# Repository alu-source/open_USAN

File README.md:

## Summary

1. Overview
2. Build instructions
3. Testing and validation 

## 1. Overview

The goal of this project was to create a low cost small scale 2D ultrasonic anenomter. The resulting solution is based on a STM32F4 microcontroller and uses off the shelf electrical components with a cost of around 100€, and offers multiple IO options for data output, a USB interface, a dual-channel analog output, and a synchronization signal input. The sensor can be configured with various parameters and a maximum measurement frequency of 100 Hz can be achieved.
A detailed explanation of the working principle and the technique used can be found in my <a href="/Documentation/Bachelor_thesis.pdf" target="_blank">thesis</a>. 
<br/><br/>
A brief explanation:

The speed of sound and the airspeed are calculated with the help of two ultrasound transmissions in opposite directions, the mean measured speed for both transmissions is the speed of sound and the difference to the mean is the airspeed.

To accurately calculate the speed of the transmissions, the time of flight (ToF) between transmission and reception must be accurately measured, which requires some neat digital signal processing.
The sensor can be used and configured via serial terminal, all commands and expected behaviour are given in the manual.

## 2. Build instructions
### Hardware
KiCad has been used for the PCB design, the design files and a production-ready export can be found in the Hardware folder.
The PCB can be manufactured by most common PCB manufacturing services such as JLCPCB or Aisler. There are two different types of PCB, a two layer PCB for mounting the transceivers and a four layer PCB for the main board. All components can be soldered by hand, although reflow soldering (using a hot plate or hot air) is highly recommended.
Most components are available from Mouser. The resistors should be 1% accurate and the ceramic capacitors should have a minimum nominal voltage rating of 24V.

The other part of the hardware consists of 3D printed parts and M3 screws.
The arms are glued into the body to create a watertight connection, an epoxy glue should be used. 

### Software
The software devlopment was done in Segger embeded studio the files can be found in the Software folder.
Further configuartion parameters can be set in the sensor_config.h file.
This makes it possible to change the transceiver or to modify the geometry of the sensor.

Using the USB interface, different runmodes an trigger/sample times can be configured, for more information look in to the [manual](https://github.com/alu-source/open-USAN/blob/main/Documentation/Manual/Ultrasonic%20Anemometer%20Reference%20Manual.docx).

## 3. Testing and Validation

Testing and validation was carried out in a wind tunnel capable of generating air speeds of up to 45 m/s.
A prantle tube and a Dantec high pression anemometer were used for velocity measurements.

In the first test, a velocity deficit was detected near the transceiver mounting location due to transceiver blockage, as shown below. 

The left plot shows the measured velocity magnetude and the right plot shows the measurement error of magnitude and angle over the inflow angle. 

In order to counteract this phenomenon, calibration was carried out at various inflow angle and air speeds. 
Each sensor has a slightly different optimum calibration, the data includes an averaged calibration for the sensor which does not give the best sensor performance but eliminates the need to perform a calibration.
A semi-automated [skript] ("/2D-US-Calibration/Skript/Sensor_calibration_and_validation.m") was developed and tested to collect the raw data required for calibration. After calibration, a validation measurement was performed.

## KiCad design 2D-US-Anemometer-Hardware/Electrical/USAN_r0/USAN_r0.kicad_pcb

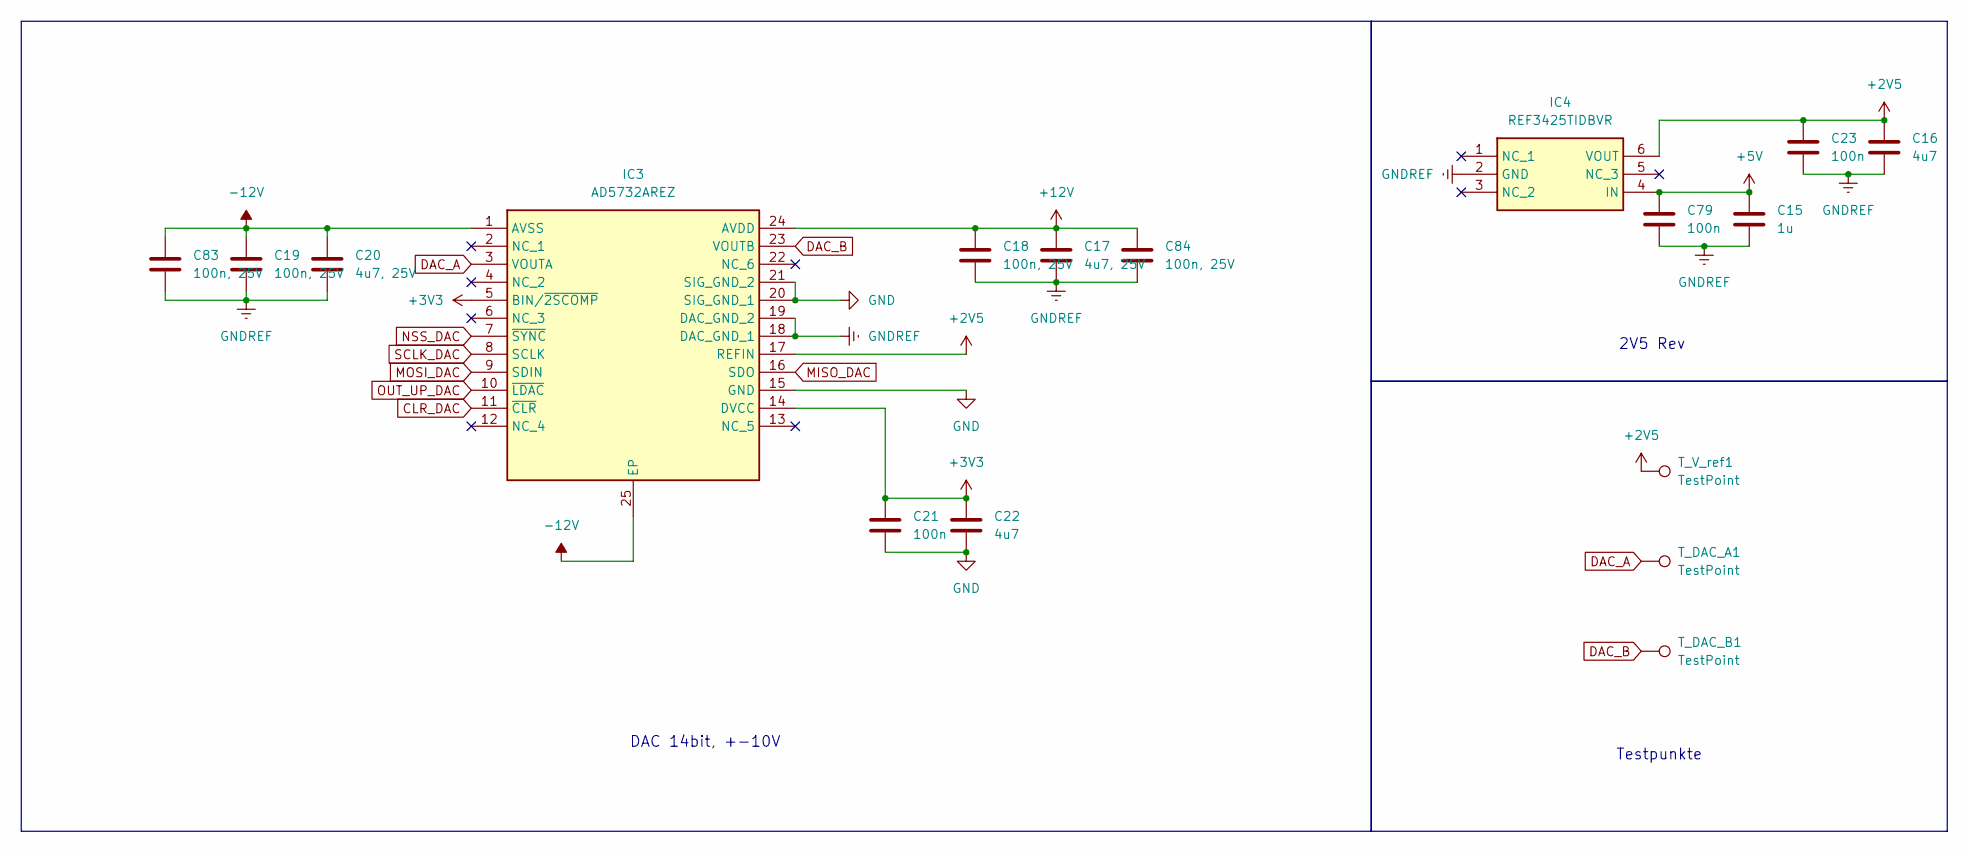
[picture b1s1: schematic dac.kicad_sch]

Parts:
C15: 1u; C_0603_1608Metric
C16, C22: 4u7; C_0805_2012Metric
C17, C20: 4u7, 25V; C_0805_2012Metric
C18, C19, C83, C84: 100n, 25V; C_0603_1608Metric
C21, C23, C79: 100n; C_0603_1608Metric
IC3: AD5732AREZ; SOP65P640X120-25N; Mouser Part Number 584-AD5732AREZ
IC4: REF3425TIDBVR; SOT95P280X145-6N; Mouser Part Number 595-REF3425TIDBVR
T_DAC_A1: TestPoint; TestPoint_Pad_D1.5mm
T_DAC_B1: TestPoint; TestPoint_Pad_D1.5mm
T_V_ref1: TestPoint; TestPoint_Pad_D1.5mm

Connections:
+2V5: C16.1, C23.1, IC3.17 (REFIN), IC4.6 (VOUT), T_V_ref1.1
+3V3: C21.1, C22.1, IC3.5 (BIN/~2SCOMP), IC3.14 (DVCC); also elsewhere on the board
+5V: C15.1, C79.1, IC4.4 (IN); also elsewhere on the board
+12V: C17.1, C18.1, C84.1, IC3.24 (AVDD); also elsewhere on the board
-12V: C19.1, C20.1, C83.1, IC3.1 (AVSS), IC3.25 (EP); also elsewhere on the board
CLR_DAC: IC3.11 (~CLR); also elsewhere on the board
DAC_A: IC3.3 (VOUTA), T_DAC_A1.1; also elsewhere on the board
DAC_B: IC3.23 (VOUTB), T_DAC_B1.1; also elsewhere on the board
GND: C21.2, C22.2, IC3.15 (GND), IC3.20 (SIG_GND_1), IC3.21 (SIG_GND_2); also elsewhere on the board
GNDREF: C15.2, C16.2, C17.2, C18.2, C19.2, C20.2, C23.2, C79.2, C83.2, C84.2, IC3.18 (DAC_GND_1), IC3.19 (DAC_GND_2), IC4.2 (GND); also elsewhere on the board
MISO_DAC: IC3.16 (SDO); also elsewhere on the board
MOSI_DAC: IC3.9 (SDIN); also elsewhere on the board
NSS_DAC: IC3.7 (~SYNC); also elsewhere on the board
OUT_UP_DAC: IC3.10 (~LDAC); also elsewhere on the board
SCLK_DAC: IC3.8 (SCLK); also elsewhere on the board

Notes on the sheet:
2V5 Rev
DAC 14bit, +-10V
Testpunkte

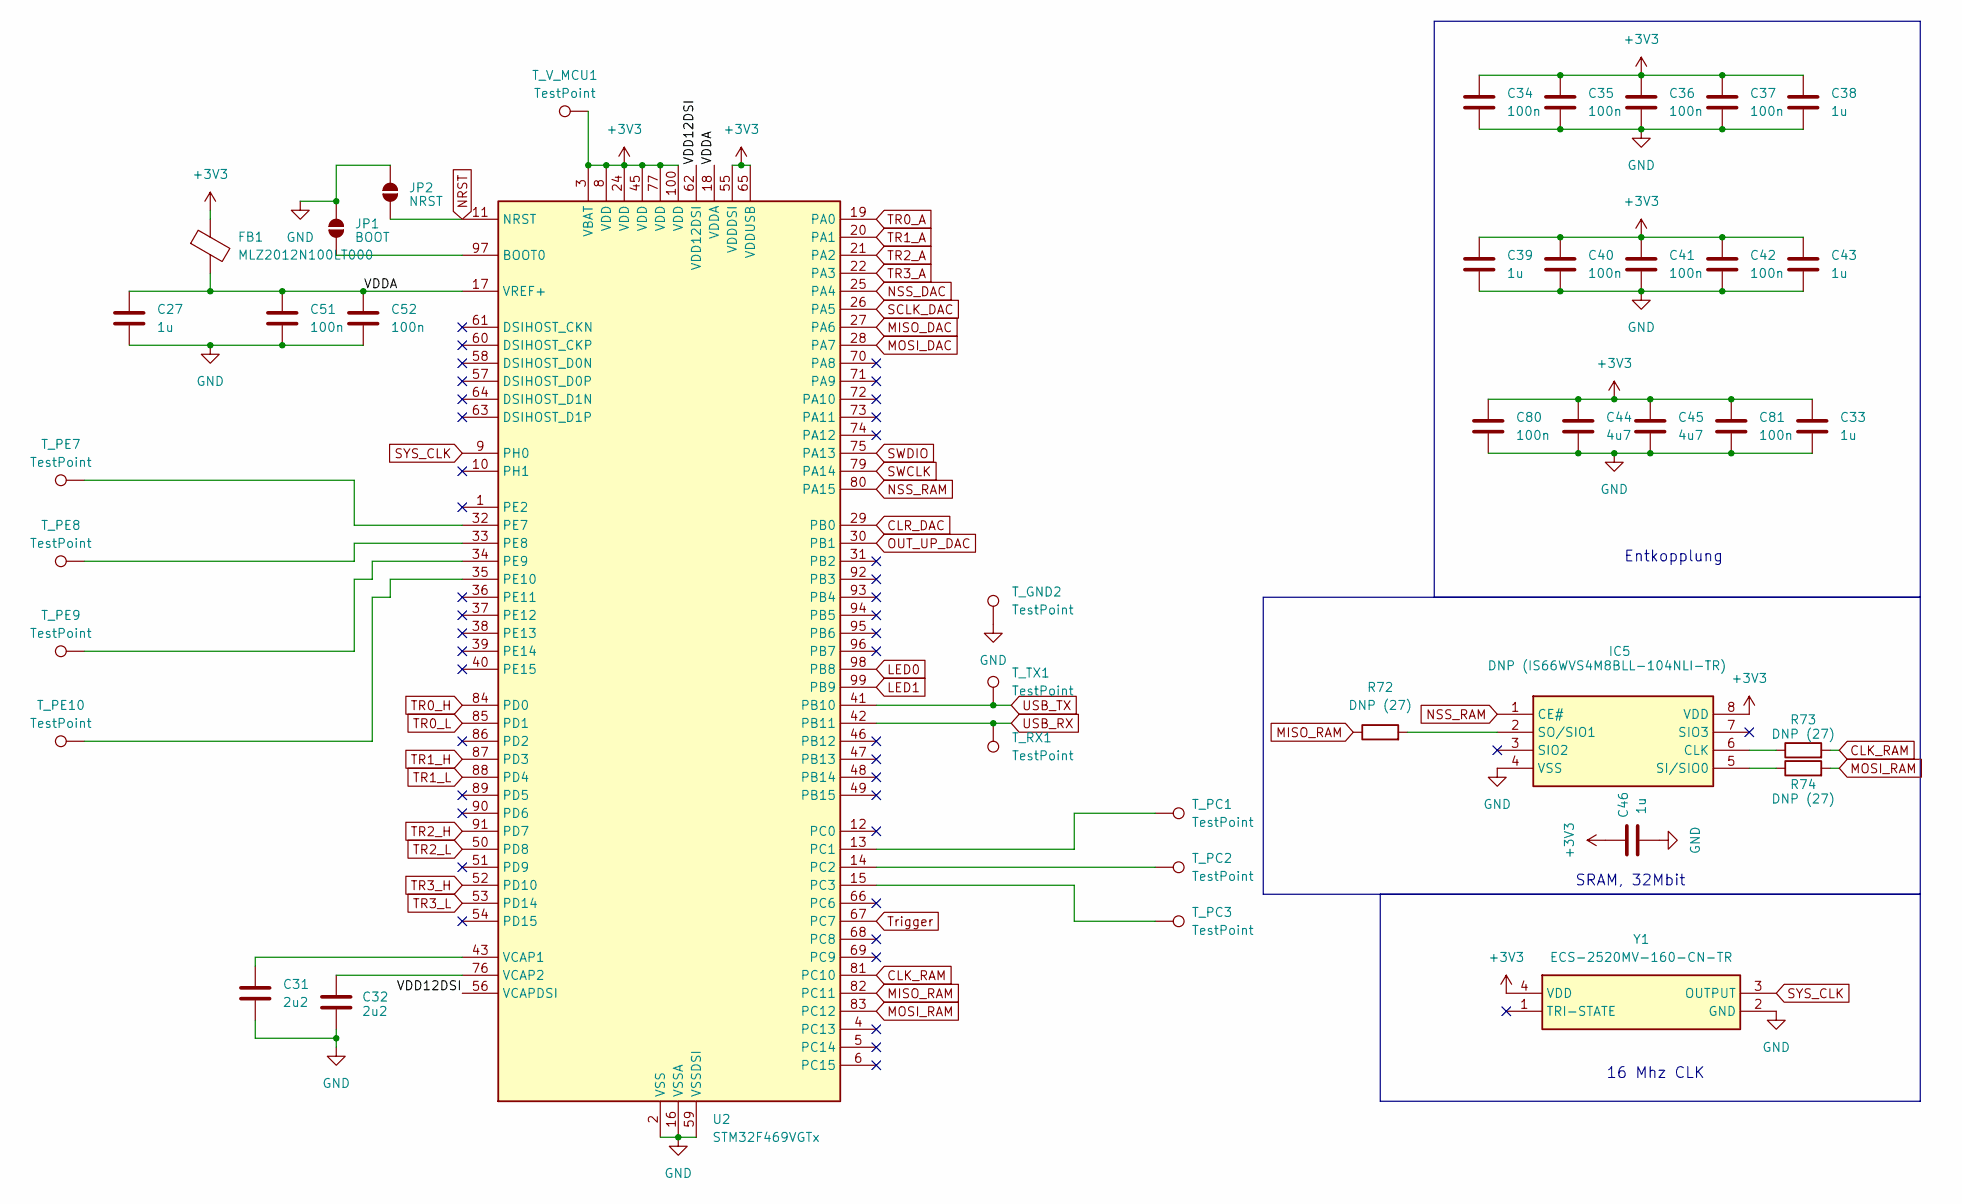
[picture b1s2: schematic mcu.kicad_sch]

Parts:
C27, C33, C38, C39, C43, C46: 1u; C_0603_1608Metric
C31, C32: 2u2; C_0603_1608Metric
C34, C35, C36, C37, C40, C41, C42, C51, C52, C80, C81: 100n; C_0603_1608Metric
C44, C45: 4u7; C_0805_2012Metric
FB1: MLZ2012N100LT000; L_0805_2012Metric
IC5: DNP (IS66WVS4M8BLL-104NLI-TR); SOIC127P600X175-8N; Mouser Part Number 870-WVS4M8BLL104NLIT
JP1: BOOT; SolderJumper-2_P1.3mm_Open_RoundedPad1.0x1.5mm
JP2: NRST; SolderJumper-2_P1.3mm_Open_RoundedPad1.0x1.5mm
R72, R73, R74: DNP (27); R_0603_1608Metric
T_GND2: TestPoint; TestPoint_Pad_D1.5mm
T_PC1, T_PC2, T_PC3: TestPoint; TestPoint_Pad_D1.5mm
T_PE7, T_PE8, T_PE9, T_PE10: TestPoint; TestPoint_Pad_D1.5mm
T_RX1: TestPoint; TestPoint_Pad_D1.5mm
T_TX1: TestPoint; TestPoint_Pad_D1.5mm
T_V_MCU1: TestPoint; TestPoint_Pad_D1.5mm
U2: STM32F469VGTx; LQFP-100_14x14mm_P0.5mm
Y1: ECS-2520MV-160-CN-TR; ECS2520MV250BNTR; Mouser Part Number 520-2520MV-160-CNT

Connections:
+3V3: C33.1, C34.1, C35.1, C36.1, C37.1, C38.1, C39.1, C40.1, C41.1, C42.1, C43.1, C44.1, C45.1, C46.2, C80.1, C81.1, FB1.1, IC5.8 (VDD), T_V_MCU1.1, U2.3 (VBAT), U2.8 (VDD), U2.24 (VDD), U2.45 (VDD), U2.55 (VDDDSI), U2.65 (VDDUSB), U2.77 (VDD), U2.100 (VDD), Y1.4 (VDD); also elsewhere on the board
/MCU/VDD12DSI: U2.56 (VCAPDSI), U2.62 (VDD12DSI)
/MCU/VDDA: C27.1, C51.1, C52.1, FB1.2, U2.17 (VREF+), U2.18 (VDDA)
CLK_RAM: R73.2, U2.81 (PC10)
CLR_DAC: U2.29 (PB0); also elsewhere on the board
GND: C27.2, C31.2, C32.2, C33.2, C34.2, C35.2, C36.2, C37.2, C38.2, C39.2, C40.2, C41.2, C42.2, C43.2, C44.2, C45.2, C46.1, C51.2, C52.2, C80.2, C81.2, IC5.4 (VSS), JP1.2 (B), JP2.2 (B), T_GND2.1, U2.2 (VSS), U2.7 (VSS), U2.16 (VSSA), U2.23 (VSS), U2.44 (VSS), U2.59 (VSSDSI), U2.78 (VSS), Y1.2 (GND); also elsewhere on the board
LED0: U2.98 (PB8); also elsewhere on the board
LED1: U2.99 (PB9); also elsewhere on the board
MISO_DAC: U2.27 (PA6); also elsewhere on the board
MISO_RAM: R72.1, U2.82 (PC11)
MOSI_DAC: U2.28 (PA7); also elsewhere on the board
MOSI_RAM: R74.2, U2.83 (PC12)
NRST: JP2.1 (A), U2.11 (NRST); also elsewhere on the board
NSS_DAC: U2.25 (PA4); also elsewhere on the board
NSS_RAM: IC5.1 (CE#), U2.80 (PA15)
unnamed: IC5.6 (CLK), R73.1
unnamed: IC5.5 (SI/SIO0), R74.1
unnamed: IC5.2 (SO/SIO1), R72.2
unnamed: JP1.1 (A), U2.97 (BOOT0)
unnamed: T_PC1.1, U2.13 (PC1)
unnamed: T_PC2.1, U2.14 (PC2)
unnamed: T_PC3.1, U2.15 (PC3)
unnamed: T_PE7.1, U2.32 (PE7)
unnamed: T_PE8.1, U2.33 (PE8)
unnamed: T_PE9.1, U2.34 (PE9)
unnamed: T_PE10.1, U2.35 (PE10)
unnamed: C31.1, U2.43 (VCAP1)
unnamed: C32.1, U2.76 (VCAP2)
OUT_UP_DAC: U2.30 (PB1); also elsewhere on the board
SCLK_DAC: U2.26 (PA5); also elsewhere on the board
SWCLK: U2.79 (PA14); also elsewhere on the board
SWDIO: U2.75 (PA13); also elsewhere on the board
SYS_CLK: U2.9 (PH0), Y1.3 (OUTPUT)
TR0_A: U2.19 (PA0); also elsewhere on the board
TR0_H: U2.84 (PD0); also elsewhere on the board
TR0_L: U2.85 (PD1); also elsewhere on the board
TR1_A: U2.20 (PA1); also elsewhere on the board
TR1_H: U2.87 (PD3); also elsewhere on the board
TR1_L: U2.88 (PD4); also elsewhere on the board
TR2_A: U2.21 (PA2); also elsewhere on the board
TR2_H: U2.91 (PD7); also elsewhere on the board
TR2_L: U2.50 (PD8); also elsewhere on the board
TR3_A: U2.22 (PA3); also elsewhere on the board
TR3_H: U2.52 (PD10); also elsewhere on the board
TR3_L: U2.53 (PD14); also elsewhere on the board
Trigger: U2.67 (PC7); also elsewhere on the board
USB_RX: T_RX1.1, U2.42 (PB11); also elsewhere on the board
USB_TX: T_TX1.1, U2.41 (PB10); also elsewhere on the board

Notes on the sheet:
Entkopplung
SRAM, 32Mbit
16 Mhz CLK

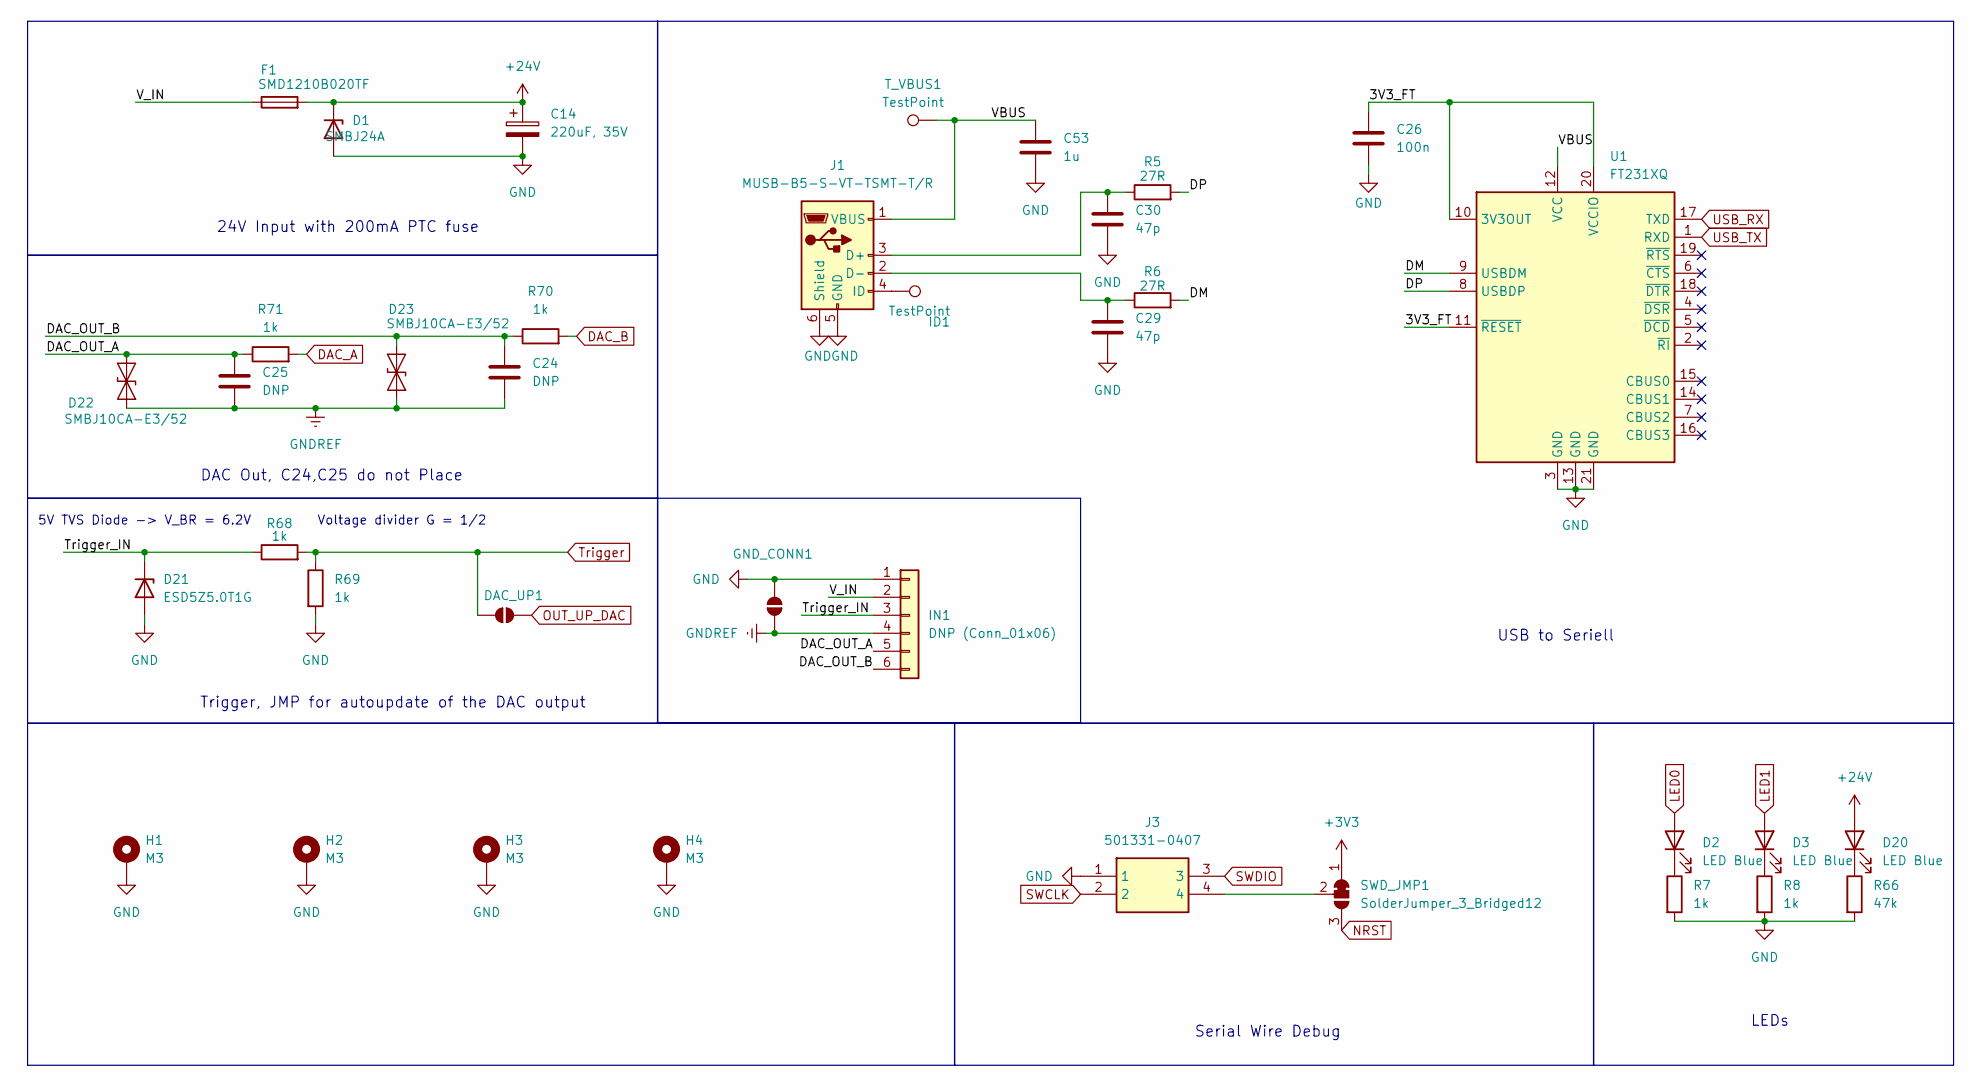
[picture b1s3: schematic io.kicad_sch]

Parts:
C14: 220uF, 35V; CP_Elec_8x10
C24, C25: DNP; C_0603_1608Metric
C26: 100n; C_0603_1608Metric
C29, C30: 47p; C_0603_1608Metric
C53: 1u; C_0603_1608Metric
D1: SMBJ24A; D_SMB
D2, D3, D20: LED Blue; LED_0603_1608Metric
D21: ESD5Z5.0T1G; D_SOD-523
D22, D23: SMBJ10CA-E3/52; D_SMB
DAC_UP1: SolderJumper_2_Open; SolderJumper-2_P1.3mm_Open_Pad1.0x1.5mm
F1: SMD1210B020TF; Fuse_1210_3225Metric
GND_CONN1: SolderJumper_2_Closed; SolderJumper-2_P1.3mm_Bridged_Pad1.0x1.5mm
H1, H2, H3, H4: M3; MountingHole_3.2mm_M3_Pad_Via
ID1: TestPoint; TestPoint_Pad_D1.5mm
IN1: DNP (Conn_01x06); PinHeader_1x06_P2.54mm_Vertical
J1: MUSB-B5-S-VT-TSMT-T/R; USB_Mini-B_AdamTech_MUSB-B5-S-VT-TSMT-1_SMD_Vertical
J3: 501331-0407; Mouser Part Number 538-501331-0407
R5, R6: 27R; R_0603_1608Metric
R7, R8, R68, R69, R70, R71: 1k; R_0603_1608Metric
R66: 47k; R_0603_1608Metric
SWD_JMP1: SolderJumper_3_Bridged12; SolderJumper-3_P1.3mm_Bridged12_RoundedPad1.0x1.5mm
T_VBUS1: TestPoint; TestPoint_Pad_D1.5mm
U1: FT231XQ; QFN-20-1EP_4x4mm_P0.5mm_EP2.5x2.5mm

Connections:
+3V3: SWD_JMP1.1 (A); also elsewhere on the board
+24V: C14.1, D1.1 (K), D20.2 (A), F1.2; also elsewhere on the board
/IO/3V3_FT: C26.1, U1.10 (3V3OUT), U1.11 (~RESET), U1.20 (VCCIO)
/IO/DAC_OUT_A: C25.1, D22.2 (A2), IN1.5, R71.1
/IO/DAC_OUT_B: C24.1, D23.2 (A2), IN1.6, R70.1
/IO/DM: R6.2, U1.9 (USBDM)
/IO/DP: R5.2, U1.8 (USBDP)
/IO/Trigger_IN: D21.1 (K), IN1.3, R68.1
/IO/VBUS: C53.1, J1.1 (VBUS), T_VBUS1.1, U1.12 (VCC)
/IO/V_IN: F1.1, IN1.2
DAC_A: R71.2; also elsewhere on the board
DAC_B: R70.2; also elsewhere on the board
GND: C14.2, C26.2, C29.2, C30.2, C53.2, D1.2 (A), D21.2 (A), GND_CONN1.2 (B), H1.MP, H2.MP, H3.MP, H4.MP, IN1.1, J1.5 (GND), J1.6 (Shield), J3.1, R7.2, R8.2, R66.2, R69.2, U1.3 (GND), U1.13 (GND), U1.21 (GND); also elsewhere on the board
GNDREF: C24.2, C25.2, D22.1 (A1), D23.1 (A1), GND_CONN1.1 (A), IN1.4; also elsewhere on the board
LED0: D2.2 (A); also elsewhere on the board
LED1: D3.2 (A); also elsewhere on the board
NRST: SWD_JMP1.3 (B); also elsewhere on the board
unnamed: D2.1 (K), R7.1
unnamed: D3.1 (K), R8.1
unnamed: D20.1 (K), R66.1
unnamed: C30.1, J1.3 (D+), R5.1
unnamed: C29.1, J1.2 (D-), R6.1
unnamed: ID1.1, J1.4 (ID)
unnamed: J3.4, SWD_JMP1.2 (C)
OUT_UP_DAC: DAC_UP1.2 (B); also elsewhere on the board
SWCLK: J3.2; also elsewhere on the board
SWDIO: J3.3; also elsewhere on the board
Trigger: DAC_UP1.1 (A), R68.2, R69.1; also elsewhere on the board
USB_RX: U1.17 (TXD); also elsewhere on the board
USB_TX: U1.1 (RXD); also elsewhere on the board

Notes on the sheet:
DAC Out, C24,C25 do not Place
24V Input with 200mA PTC fuse
LEDs
Trigger, JMP for autoupdate of the DAC output
Serial Wire Debug
USB to Seriell
5V TVS Diode -> V_BR = 6.2V
Voltage divider G = 1/2

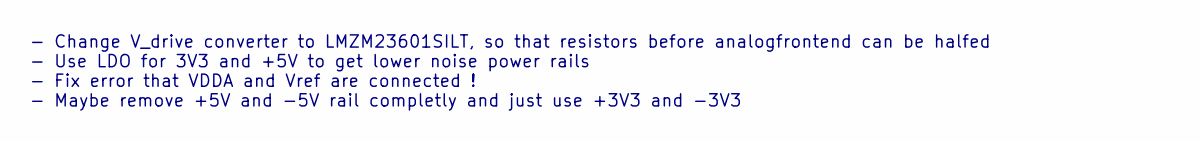
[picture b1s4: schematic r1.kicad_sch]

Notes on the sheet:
- Change V_drive converter to LMZM23601SILT, so that resistors before analogfrontend can be halfed - Use LDO for 3V3 and +5V to get lower noise power rails - Fix error that VDDA and Vref are connected ! - Maybe remove +5V and -5V rail completly and just use +3V3 and -3V3

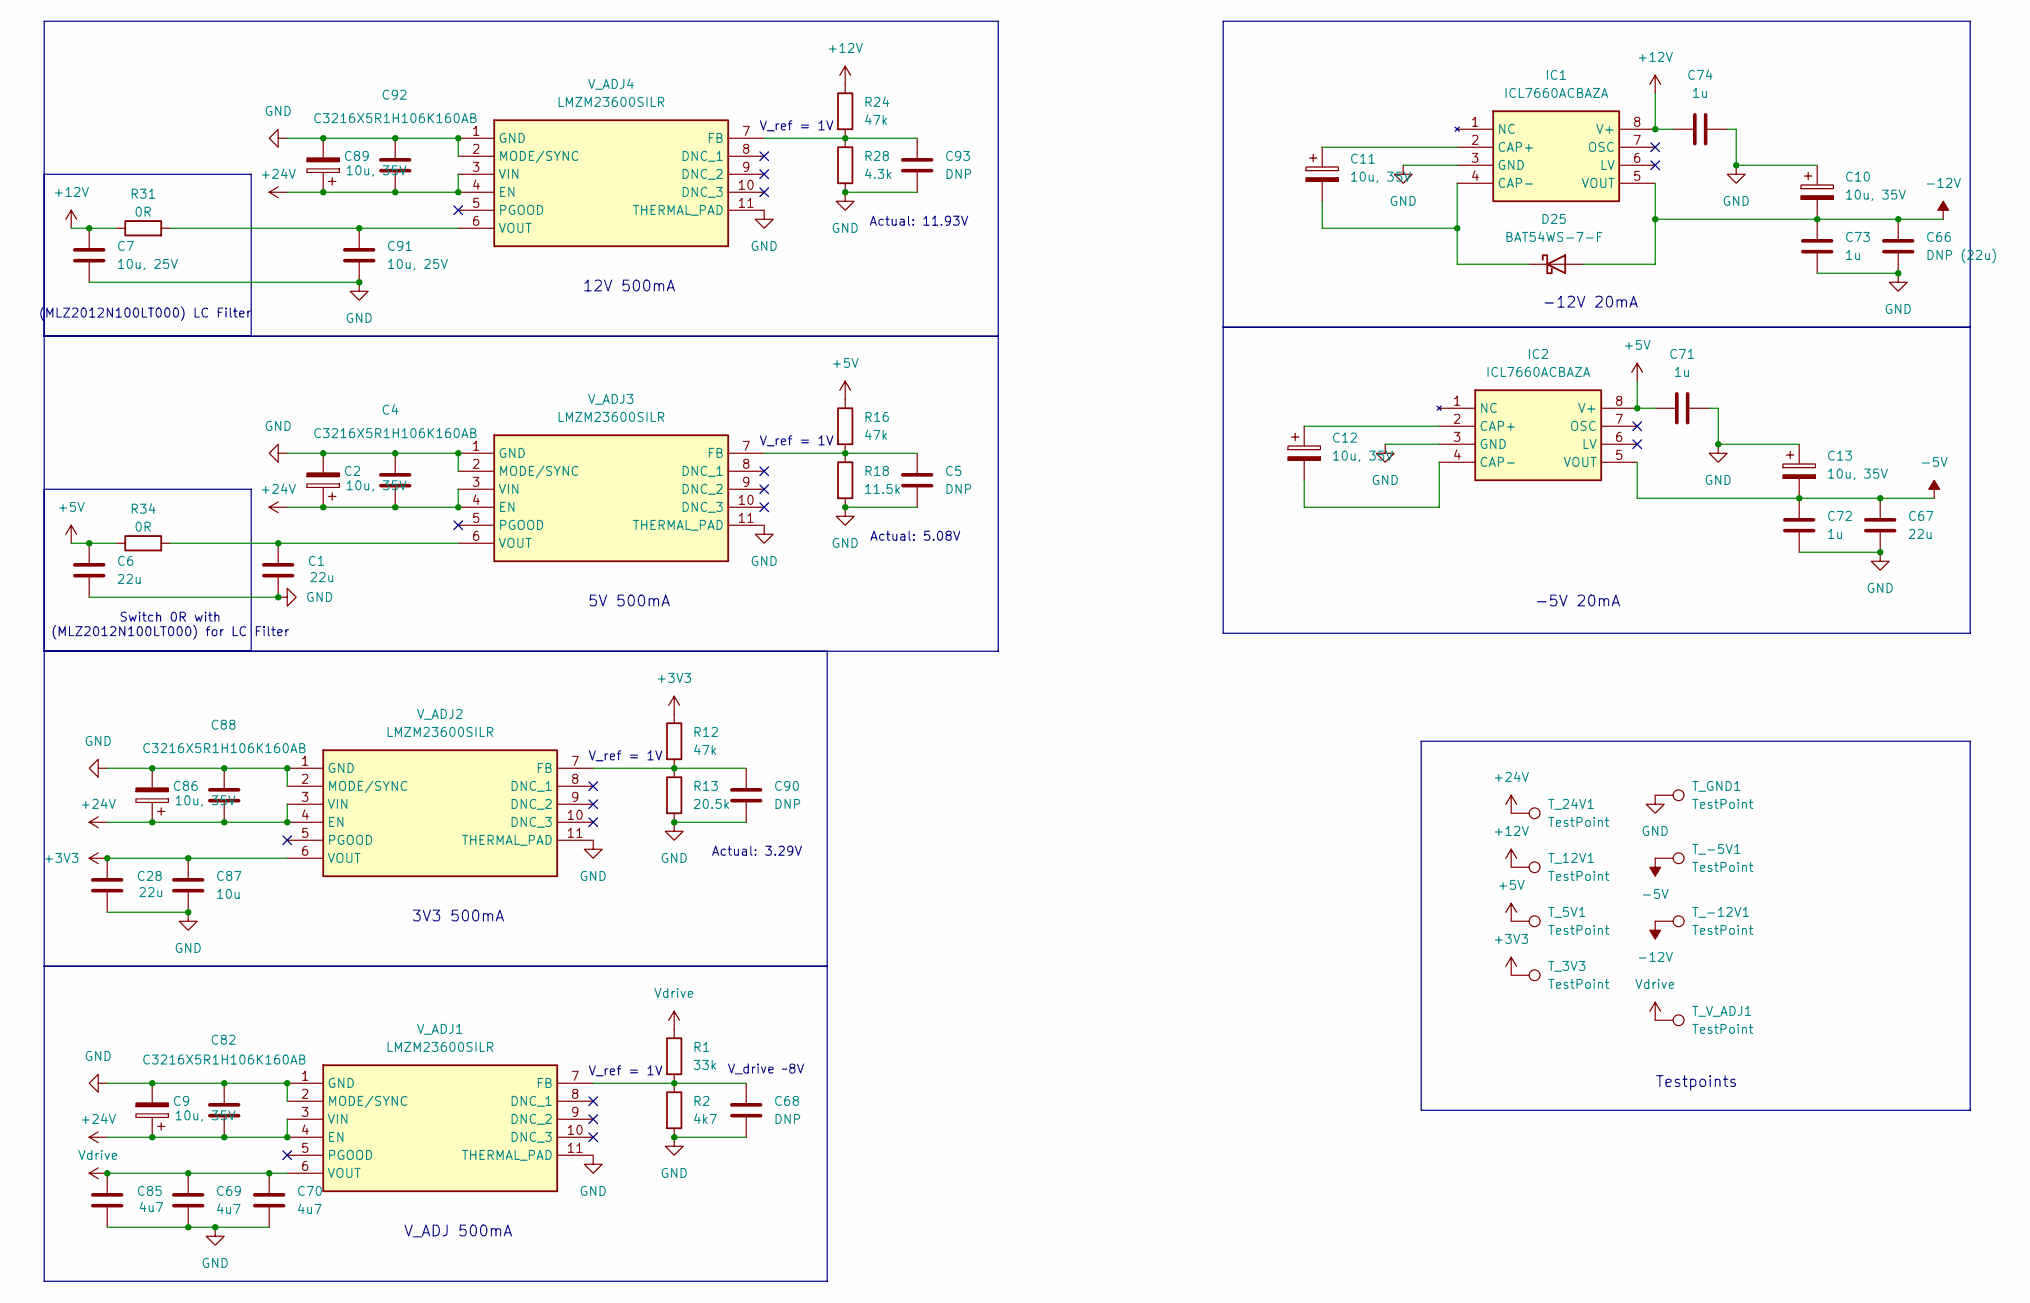
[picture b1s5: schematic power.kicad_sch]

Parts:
C1, C6, C28, C67: 22u; C_0805_2012Metric
C2, C9, C10, C11, C12, C13, C86, C89: 10u, 35V; CP_Elec_4x5.4
C4, C82, C88, C92: C3216X5R1H106K160AB; C_1206_3216Metric
C5, C68, C90, C93: DNP; C_0603_1608Metric
C7, C91: 10u, 25V; C_0805_2012Metric
C66: DNP (22u); C_0805_2012Metric
C69, C70, C85: 4u7; C_0805_2012Metric
C71, C72, C73, C74: 1u; C_0603_1608Metric
C87: 10u; C_0805_2012Metric
D25: BAT54WS-7-F; D_SOD-323
IC1, IC2: ICL7660ACBAZA; SOIC127P600X175-8N; Mouser Part Number 968-ICL7660CBAZA-T
R1: 33k; R_0603_1608Metric
R2: 4k7; R_0603_1608Metric
R12, R16, R24: 47k; R_0603_1608Metric
R13: 20.5k; R_0603_1608Metric
R18: 11.5k; R_0603_1608Metric
R28: 4.3k; R_0603_1608Metric
R31, R34: 0R; R_0805_2012Metric
T_3V3, T_5V1, T_12V1, T_24V1: TestPoint; TestPoint_Pad_D1.5mm
T_-5V1, T_-12V1: TestPoint; TestPoint_Pad_D1.5mm
T_GND1: TestPoint; TestPoint_Pad_D1.5mm
T_V_ADJ1: TestPoint; TestPoint_Pad_D1.5mm
V_ADJ1, V_ADJ2, V_ADJ3, V_ADJ4: LMZM23600SILR; LMZM23600SILT; Mouser Part Number 595-LMZM23600SILR

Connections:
+3V3: C28.1, C87.1, R12.1, T_3V3.1, V_ADJ2.6 (VOUT); also elsewhere on the board
+5V: C6.1, C71.2, IC2.8 (V+), R16.1, R34.1, T_5V1.1; also elsewhere on the board
+12V: C7.1, C74.1, IC1.8 (V+), R24.1, R31.1, T_12V1.1; also elsewhere on the board
+24V: C2.1, C4.2, C9.1, C82.2, C86.1, C88.2, C89.1, C92.2, T_24V1.1, V_ADJ1.3 (VIN), V_ADJ1.4 (EN), V_ADJ2.3 (VIN), V_ADJ2.4 (EN), V_ADJ3.3 (VIN), V_ADJ3.4 (EN), V_ADJ4.3 (VIN), V_ADJ4.4 (EN); also elsewhere on the board
-5V: C13.2, C67.1, C72.1, IC2.5 (VOUT), T_-5V1.1; also elsewhere on the board
-12V: C10.2, C66.1, C73.1, D25.2 (A), IC1.5 (VOUT), T_-12V1.1; also elsewhere on the board
GND: C1.2, C2.2, C4.1, C5.2, C6.2, C7.2, C9.2, C10.1, C13.1, C28.2, C66.2, C67.2, C68.2, C69.2, C70.2, C71.1, C72.2, C73.2, C74.2, C82.1, C85.2, C86.2, C87.2, C88.1, C89.2, C90.2, C91.2, C92.1, C93.2, IC1.3 (GND), IC2.3 (GND), R2.2, R13.2, R18.2, R28.2, T_GND1.1, V_ADJ1.1 (GND), V_ADJ1.2 (MODE/SYNC), V_ADJ1.11 (THERMAL_PAD), V_ADJ2.1 (GND), V_ADJ2.2 (MODE/SYNC), V_ADJ2.11 (THERMAL_PAD), V_ADJ3.1 (GND), V_ADJ3.2 (MODE/SYNC), V_ADJ3.11 (THERMAL_PAD), V_ADJ4.1 (GND), V_ADJ4.2 (MODE/SYNC), V_ADJ4.11 (THERMAL_PAD); also elsewhere on the board
unnamed: C11.2, D25.1 (K), IC1.4 (CAP-)
unnamed: C11.1, IC1.2 (CAP+)
unnamed: C12.1, IC2.2 (CAP+)
unnamed: C12.2, IC2.4 (CAP-)
unnamed: C68.1, R1.2, R2.1, V_ADJ1.7 (FB)
unnamed: C90.1, R12.2, R13.1, V_ADJ2.7 (FB)
unnamed: C5.1, R16.2, R18.1, V_ADJ3.7 (FB)
unnamed: C1.1, R34.2, V_ADJ3.6 (VOUT)
unnamed: C93.1, R24.2, R28.1, V_ADJ4.7 (FB)
unnamed: C91.1, R31.2, V_ADJ4.6 (VOUT)
Vdrive: C69.1, C70.1, C85.1, R1.1, T_V_ADJ1.1, V_ADJ1.6 (VOUT); also elsewhere on the board

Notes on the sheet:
V_ref = 1V
-5V 20mA
V_drive ~8V
Actual: 5.08V
Switch 0R with (MLZ2012N100LT000) for LC Filter
3V3 500mA
Actual: 11.93V
(MLZ2012N100LT000) LC Filter
5V 500mA
Actual: 3.29V
Testpoints
-12V 20mA
12V 500mA
V_ADJ 500mA

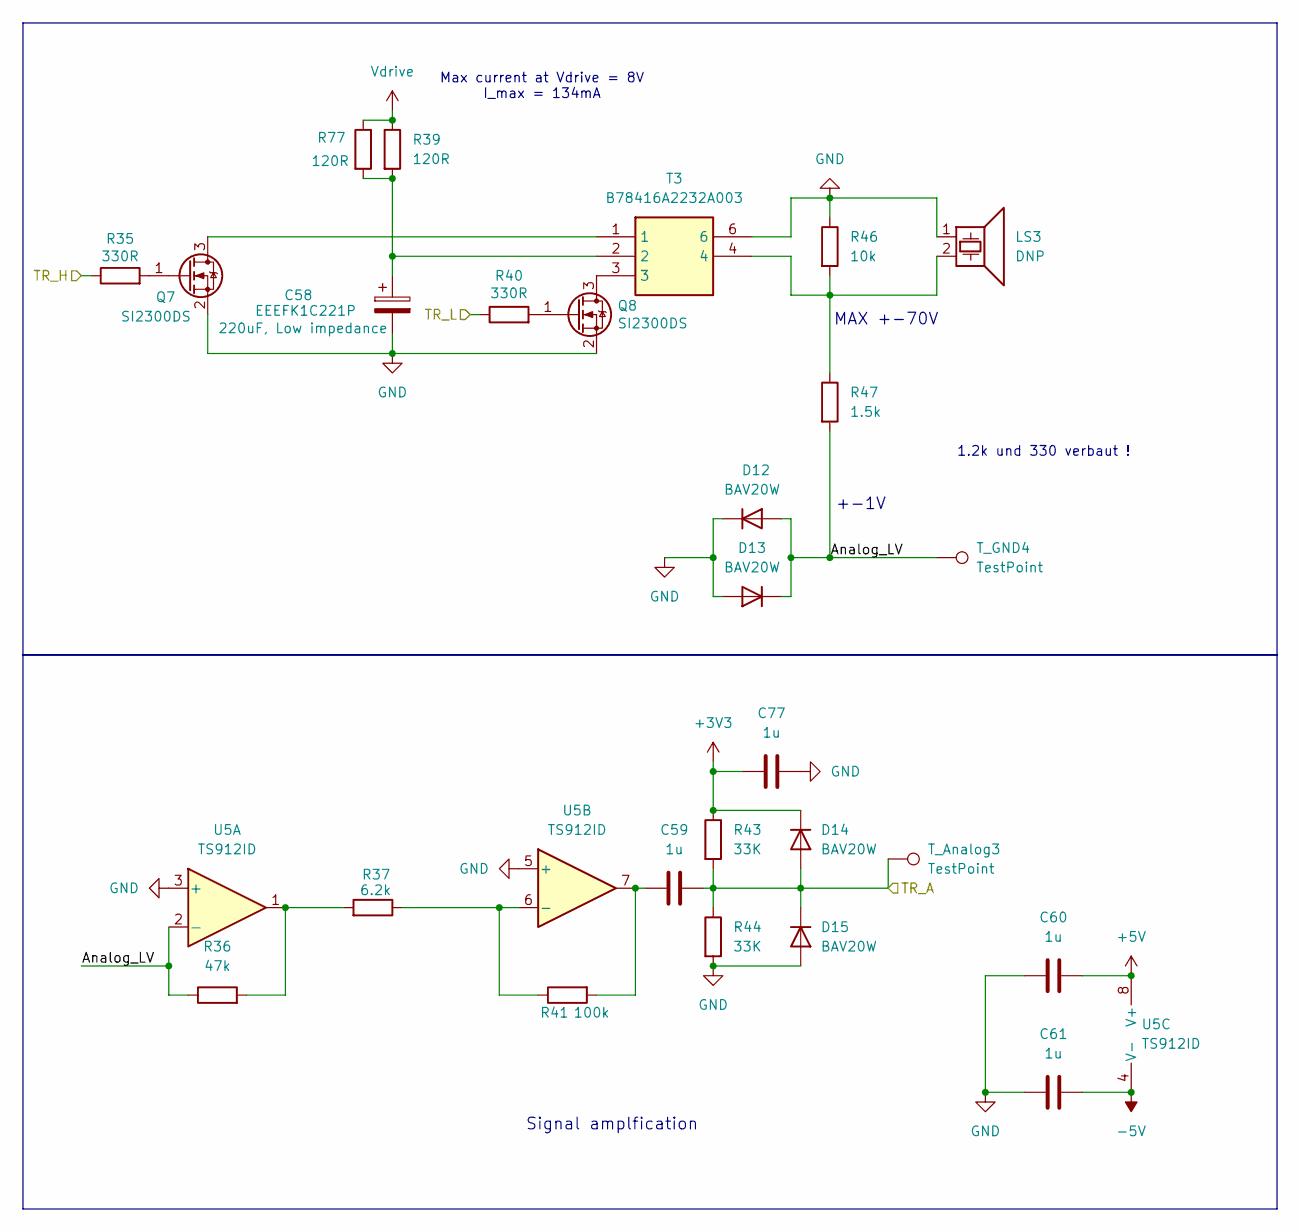
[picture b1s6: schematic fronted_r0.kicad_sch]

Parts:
C58: EEEFK1C221P; CP_Elec_8x6.2
C59, C60, C61, C77: 1u; C_0603_1608Metric
D12, D13, D14, D15: BAV20W; D_SOD-123
LS3: DNP; US_Solderpad
Q7, Q8: SI2300DS; SOT-23-3
R35, R40: 330R; R_0603_1608Metric
R36: 47k; R_0603_1608Metric
R37: 6.2k; R_0603_1608Metric
R39, R77: 120R; R_0603_1608Metric
R41: 100k; R_0603_1608Metric
R43, R44: 33K; R_0603_1608Metric
R46: 10k; R_0603_1608Metric
R47: 1.5k; R_0603_1608Metric
T3: B78416A2232A003; Mouser Part Number 871-B78416A2232A003
T_Analog3: TestPoint; TestPoint_Pad_D1.5mm
T_GND4: TestPoint; TestPoint_Pad_D1.5mm
U5: TS912ID; SOIC-8_3.9x4.9mm_P1.27mm

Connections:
+3V3: C77.1, D14.1 (K), R43.1; also elsewhere on the board
+5V: C60.2, U5.8 (V+); also elsewhere on the board
-5V: C61.2, U5.4 (V-); also elsewhere on the board
/Analog/frontend_2/Analog_LV: D12.2 (A), D13.1 (K), R36.1, R47.2, T_GND4.1, U5.2 (-)
GND: C58.2, C60.1, C61.1, C77.2, D12.1 (K), D13.2 (A), D15.2 (A), LS3.1, Q7.2 (S), Q8.2 (S), R44.2, R46.1, T3.6, U5.3 (+), U5.5 (+); also elsewhere on the board
unnamed: C58.1, R39.2, R77.2, T3.2
unnamed: C59.1, R41.2, U5.7
unnamed: LS3.2, R46.2, R47.1, T3.4
unnamed: Q7.3 (D), T3.1
unnamed: Q7.1 (G), R35.2
unnamed: Q8.3 (D), T3.3
unnamed: Q8.1 (G), R40.2
unnamed: R36.2, R37.2, U5.1
unnamed: R37.1, R41.1, U5.6 (-)
TR2_A: C59.2, D14.2 (A), D15.1 (K), R43.2, R44.1, T_Analog3.1; also elsewhere on the board
TR2_H: R35.1; also elsewhere on the board
TR2_L: R40.1; also elsewhere on the board
Vdrive: R39.1, R77.1; also elsewhere on the board

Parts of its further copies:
C47, C49, C50, C55, C56, C57, C63, C64, C65, C75, C76, C78: 1u; C_0603_1608Metric
C48, C54, C62: EEEFK1C221P; CP_Elec_8x6.2
D4, D5, D6, D7, D8, D9, D10, D11, D16, D17, D18, D19: BAV20W; D_SOD-123
LS1, LS2, LS4: DNP; US_Solderpad
Q1, Q2, Q4, Q5, Q10, Q11: SI2300DS; SOT-23-3
R3, R25, R53, R75, R76, R78: 120R; R_0603_1608Metric
R4, R9, R21, R26, R49, R54: 330R; R_0603_1608Metric
R10, R32, R60: 10k; R_0603_1608Metric
R11, R33, R61: 1.5k; R_0603_1608Metric
R14, R22, R50: 47k; R_0603_1608Metric
R15, R23, R51: 6.2k; R_0603_1608Metric
R17, R27, R55: 100k; R_0603_1608Metric
R19, R20, R29, R30, R57, R58: 33K; R_0603_1608Metric
T1, T2, T4: B78416A2232A003; Mouser Part Number 871-B78416A2232A003
T_Analog1, T_Analog2, T_Analog4: TestPoint; TestPoint_Pad_D1.5mm
T_GND3, T_GND5: TestPoint; TestPoint_Pad_D1.5mm
T_TR_A1: TestPoint; TestPoint_Pad_D1.5mm
U3, U4, U6: TS912ID; SOIC-8_3.9x4.9mm_P1.27mm

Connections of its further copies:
+3V3: C75.1, C76.1, C78.1, D6.1 (K), D10.1 (K), D18.1 (K), R20.1, R29.1, R57.1; also elsewhere on the board
+5V: C47.2, C56.2, C64.2, U3.8 (V+), U4.8 (V+), U6.8 (V+); also elsewhere on the board
-5V: C49.2, C57.2, C65.2, U3.4 (V-), U4.4 (V-), U6.4 (V-); also elsewhere on the board
/Analog/frontend_0/Analog_LV: D4.2 (A), D5.1 (K), R11.2, R14.1, T_Analog1.1, U3.2 (-)
/Analog/frontend_1/Analog_LV: D8.2 (A), D9.1 (K), R22.1, R33.2, T_GND3.1, U4.2 (-)
/Analog/frontend_3/Analog_LV: D16.2 (A), D17.1 (K), R50.1, R61.2, T_GND5.1, U6.2 (-)
GND: C47.1, C48.2, C49.1, C54.2, C56.1, C57.1, C62.2, C64.1, C65.1, C75.2, C76.2, C78.2, D4.1 (K), D5.2 (A), D7.2 (A), D8.1 (K), D9.2 (A), D11.2 (A), D16.1 (K), D17.2 (A), D19.2 (A), LS1.1, LS2.1, LS4.1, Q1.2 (S), Q2.2 (S), Q4.2 (S), Q5.2 (S), Q10.2 (S), Q11.2 (S), R10.1, R19.2, R30.2, R32.1, R58.2, R60.1, T1.6, T2.6, T4.6, U3.3 (+), U3.5 (+), U4.3 (+), U4.5 (+), U6.3 (+), U6.5 (+); also elsewhere on the board
unnamed: C48.1, R3.2, R75.2, T1.2
unnamed: C50.1, R17.2, U3.7
unnamed: C54.1, R25.2, R76.2, T2.2
unnamed: C55.1, R27.2, U4.7
unnamed: C62.1, R53.2, R78.2, T4.2
unnamed: C63.1, R55.2, U6.7
unnamed: LS1.2, R10.2, R11.1, T1.4
unnamed: LS2.2, R32.2, R33.1, T2.4
unnamed: LS4.2, R60.2, R61.1, T4.4
unnamed: Q1.3 (D), T1.1
unnamed: Q1.1 (G), R4.2
unnamed: Q2.3 (D), T1.3
unnamed: Q2.1 (G), R9.2
unnamed: Q4.3 (D), T2.1
unnamed: Q4.1 (G), R21.2
unnamed: Q5.3 (D), T2.3
unnamed: Q5.1 (G), R26.2
unnamed: Q10.3 (D), T4.1
unnamed: Q10.1 (G), R49.2
unnamed: Q11.3 (D), T4.3
unnamed: Q11.1 (G), R54.2
unnamed: R14.2, R15.2, U3.1
unnamed: R22.2, R23.2, U4.1
unnamed: R50.2, R51.2, U6.1
unnamed: R15.1, R17.1, U3.6 (-)
unnamed: R23.1, R27.1, U4.6 (-)
unnamed: R51.1, R55.1, U6.6 (-)
TR0_A: C50.2, D6.2 (A), D7.1 (K), R19.1, R20.2, T_TR_A1.1; also elsewhere on the board
TR0_H: R4.1; also elsewhere on the board
TR0_L: R9.1; also elsewhere on the board
TR1_A: C55.2, D10.2 (A), D11.1 (K), R29.2, R30.1, T_Analog2.1; also elsewhere on the board
TR1_H: R21.1; also elsewhere on the board
TR1_L: R26.1; also elsewhere on the board
TR3_A: C63.2, D18.2 (A), D19.1 (K), R57.2, R58.1, T_Analog4.1; also elsewhere on the board
TR3_H: R49.1; also elsewhere on the board
TR3_L: R54.1; also elsewhere on the board
Vdrive: R3.1, R25.1, R53.1, R75.1, R76.1, R78.1; also elsewhere on the board

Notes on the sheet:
MAX +-70V
+-1V
1.2k und 330 verbaut !
Max current at Vdrive = 8V I_max = 134mA
Signal amplfication
